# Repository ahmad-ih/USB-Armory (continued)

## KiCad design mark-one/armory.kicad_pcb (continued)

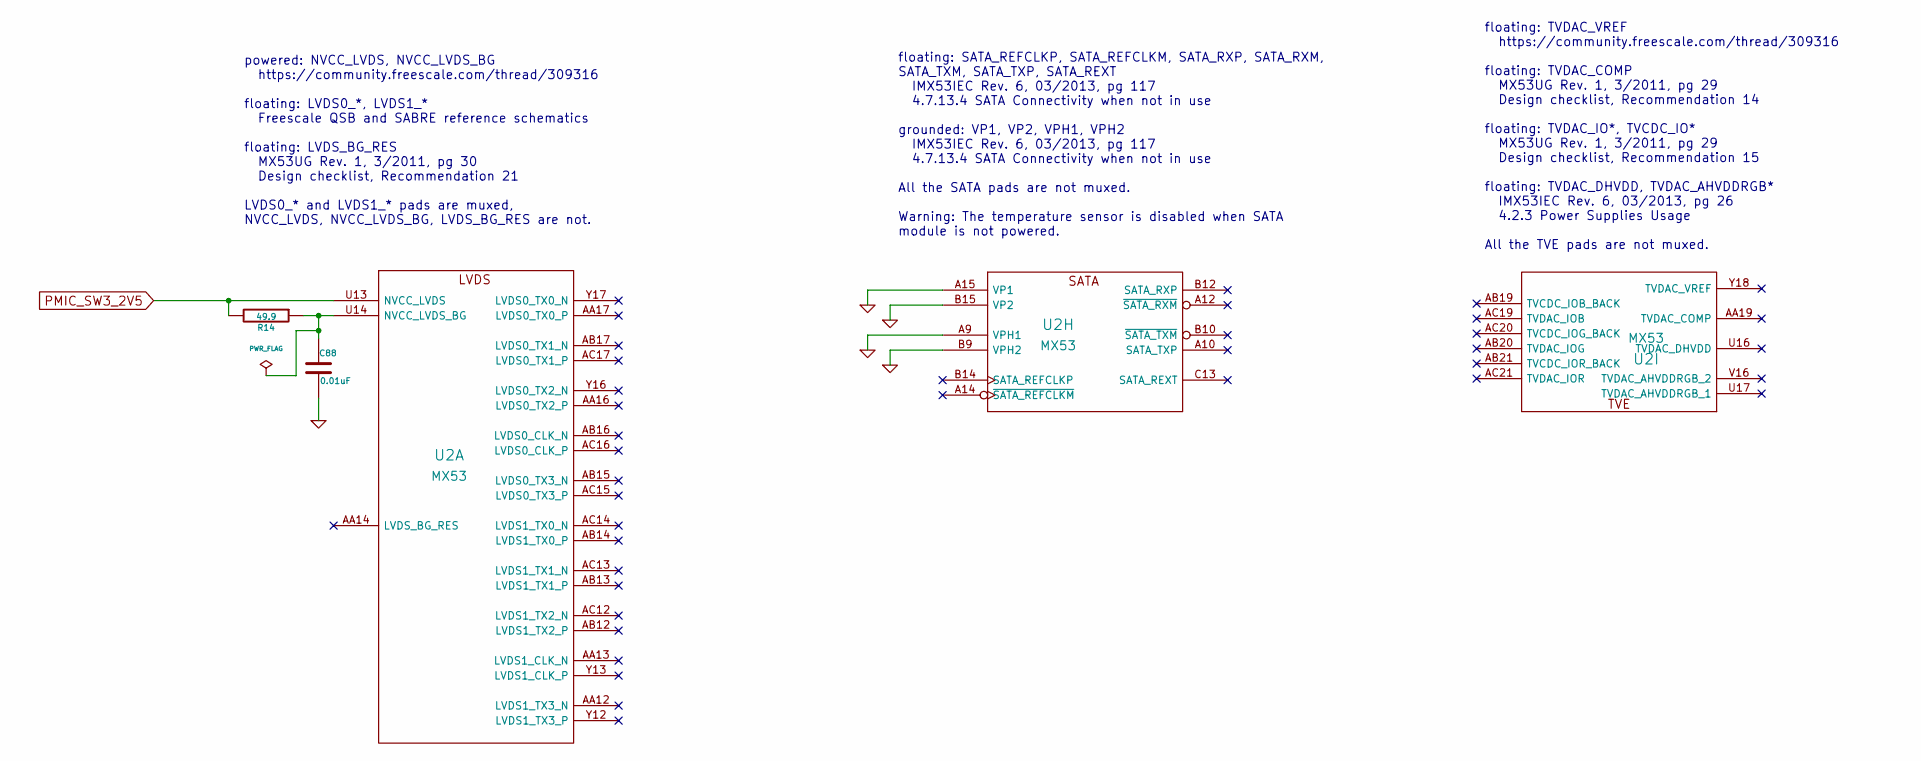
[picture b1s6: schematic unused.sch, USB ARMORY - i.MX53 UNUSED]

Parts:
C88: 0.01uF; SM0201; Mfg PN C0603X7R1A103K030BA
R14: 49.9; SM0201; Mfg PN CRCW020149R9FNED
U2: MX53

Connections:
GND: C88.2, U2.A9 (VPH1), U2.A15 (VP1), U2.B9 (VPH2), U2.B15 (VP2); also elsewhere on the board
unnamed: C88.1, R14.1, U2.U14 (NVCC_LVDS_BG)
PMIC_SW3_2V5: R14.2, U2.U13 (NVCC_LVDS); also elsewhere on the board

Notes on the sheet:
floating: TVDAC_VREF https://community.freescale.com/thread/309316 floating: TVDAC_COMP MX53UG Rev. 1, 3/2011, pg 29 Design checklist, Recommendation 14 floating: TVDAC_IO*, TVCDC_IO* MX53UG Rev. 1, 3/2011, pg 29 Design checklist, Recommendation 15 floating: TVDAC_DHVDD, TVDAC_AHVDDRGB* IMX53IEC Re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
powered: NVCC_LVDS, NVCC_LVDS_BG https://community.freescale.com/thread/309316 floating: LVDS0_*, LVDS1_* Freescale QSB and SABRE reference schematics floating: LVDS_BG_RES MX53UG Rev. 1, 3/2011, pg 30 Design checklist, Recommendation 21 LVDS0_* and LVDS1_* pads are muxed, NVCC_LVDS, NVCC_LVDS_BG, 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
floating: SATA_REFCLKP, SATA_REFCLKM, SATA_RXP, SATA_RXM, SATA_TXM, SATA_TXP, SATA_REXT IMX53IEC Rev. 6, 03/2013, pg 117 4.7.13.4 SATA Connectivity when not in use grounded: VP1, VP2, VPH1, VPH2 IMX53IEC Rev. 6, 03/2013, pg 117 4.7.13.4 SATA Connectivity when not in use All the SATA pads are not mu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

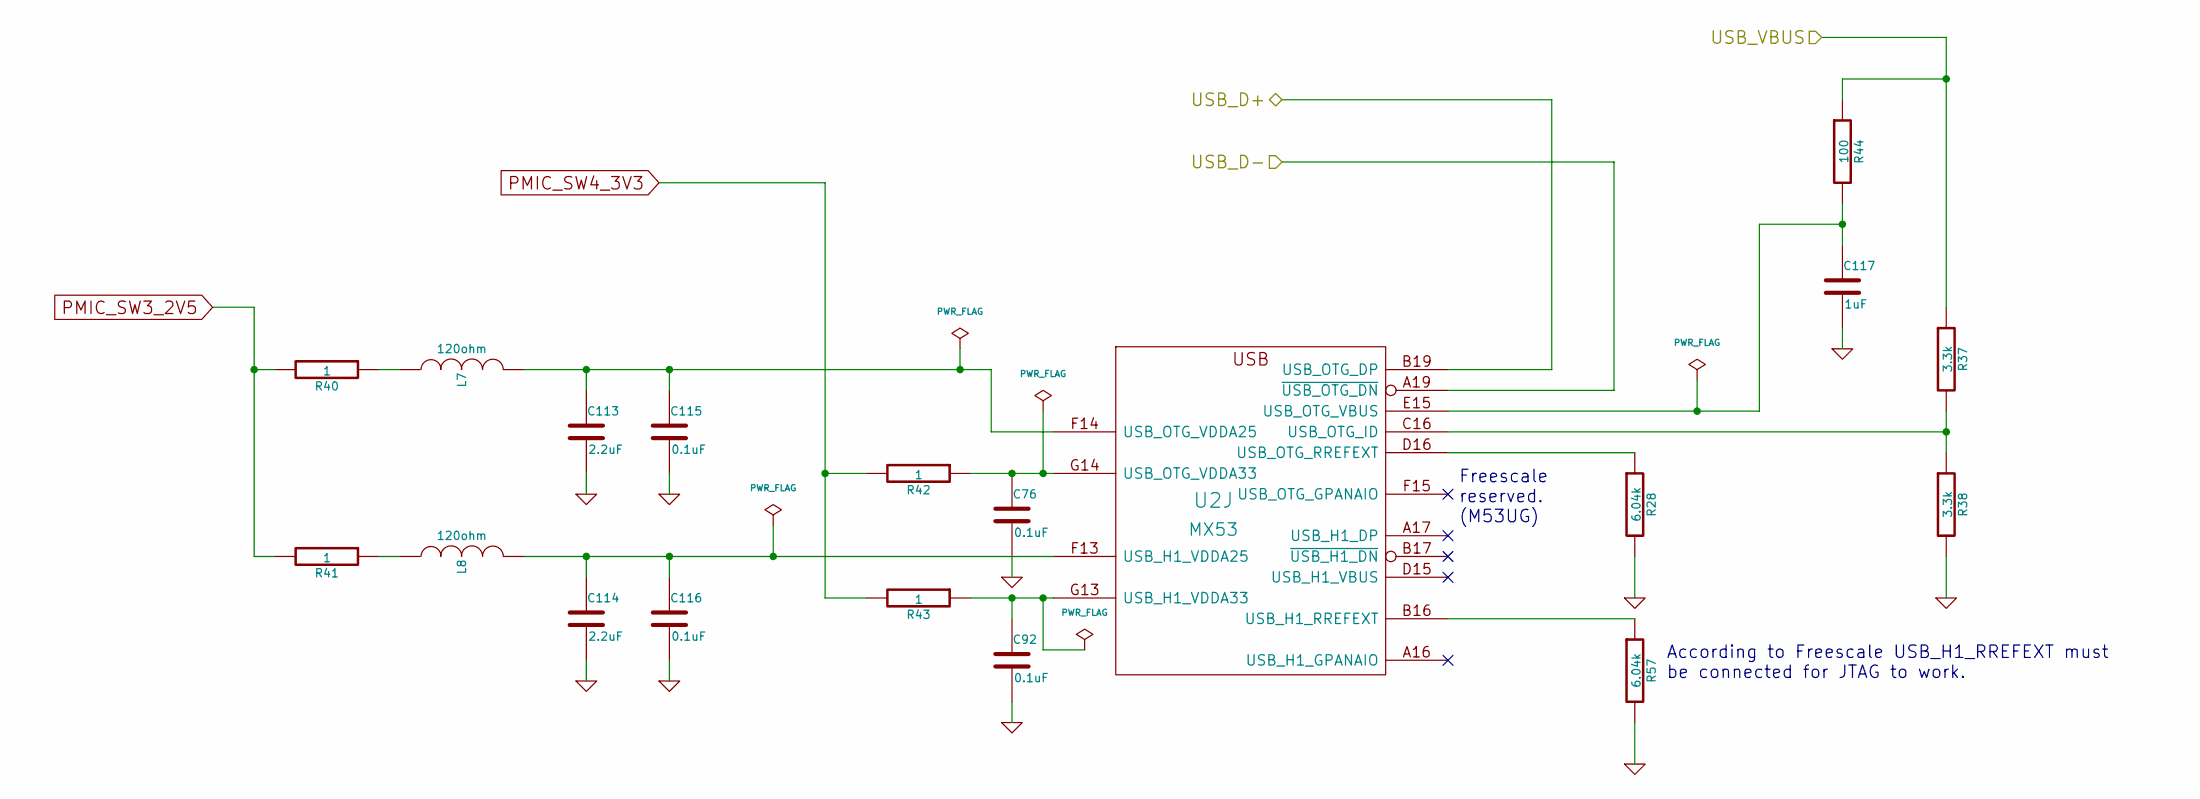
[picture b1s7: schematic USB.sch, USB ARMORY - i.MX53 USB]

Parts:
C76, C92, C115, C116: 0.1uF; SM0201; Mfg PN C0603X5R0J104K030BC
C113, C114: 2.2uF; SM0402; Mfg PN C1005X5R0J225K050BC
C117: 1uF; SM0201; Mfg PN C0603X5R0J105M030BC
L7, L8: 120ohm; SM0201; Mfg PN 742692003
R28, R57: 6.04k; SM0201; Mfg PN CRCW02016K04FNED
R37, R38: 3.3k; SM0201; Mfg PN CRCW02013K30FNED
R40, R41, R42, R43: 1; SM0201; Mfg PN MCRE000220
R44: 100; SM0201; Mfg PN CRCW0201100RFNED
U2: MX53

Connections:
/Interfaces/USB_VBUS: R37.1, R44.1; also elsewhere on the board
/USB/USB_D+: U2.B19 (USB_OTG_DP); also elsewhere on the board
/USB/USB_D-: U2.A19 (~USB_OTG_DN); also elsewhere on the board
GND: C76.2, C92.2, C113.2, C114.2, C115.2, C116.2, C117.2, R28.2, R38.2, R57.2; also elsewhere on the board
unnamed: C76.1, R42.1, U2.G14 (USB_OTG_VDDA33)
unnamed: C92.1, R43.1, U2.G13 (USB_H1_VDDA33)
unnamed: C113.1, C115.1, L7.2, U2.F14 (USB_OTG_VDDA25)
unnamed: C114.1, C116.1, L8.2, U2.F13 (USB_H1_VDDA25)
unnamed: C117.1, R44.2, U2.E15 (USB_OTG_VBUS)
unnamed: L7.1, R40.1
unnamed: L8.1, R41.1
unnamed: R28.1, U2.D16 (USB_OTG_RREFEXT)
unnamed: R37.2, R38.1, U2.C16 (USB_OTG_ID)
unnamed: R57.1, U2.B16 (USB_H1_RREFEXT)
PMIC_SW3_2V5: R40.2, R41.2; also elsewhere on the board
PMIC_SW4_3V3: R42.2, R43.2; also elsewhere on the board

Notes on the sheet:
Freescale reserved. (M53UG)
According to Freescale USB_H1_RREFEXT must be connected for JTAG to work.

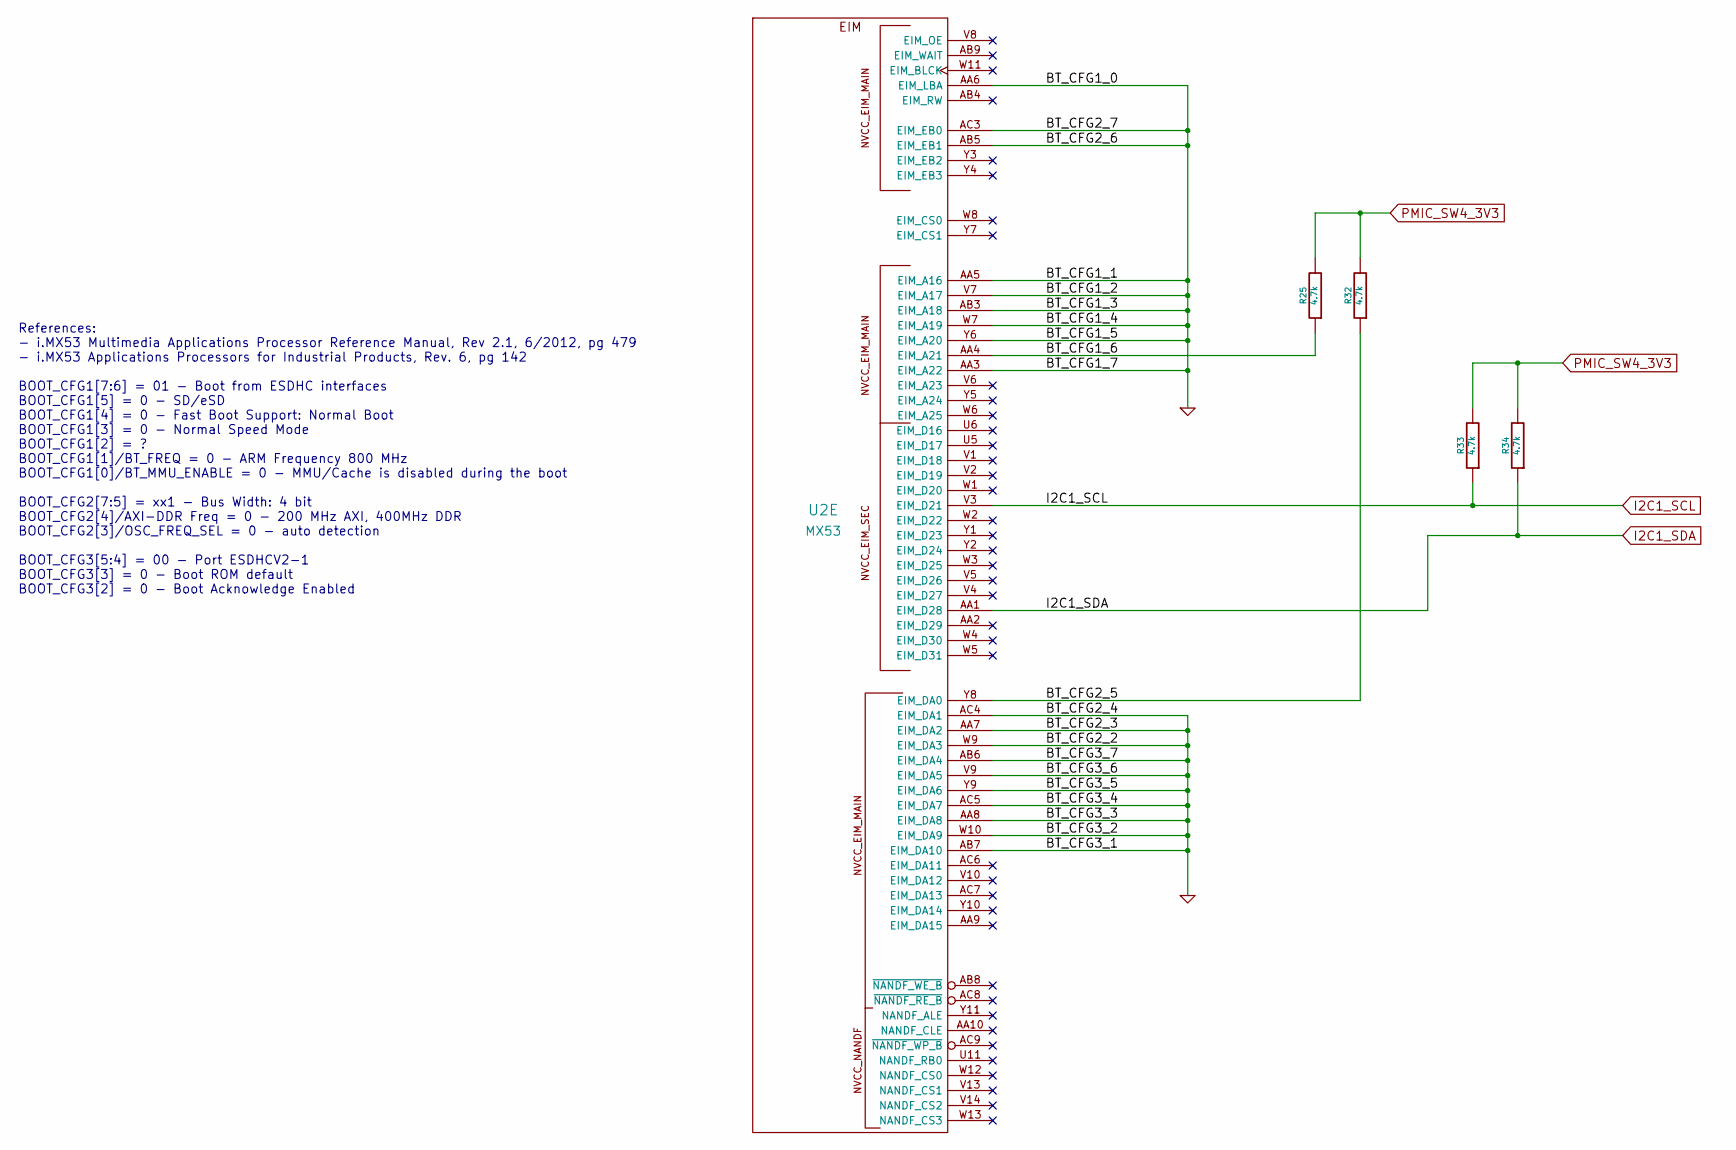
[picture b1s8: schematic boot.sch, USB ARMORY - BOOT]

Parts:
R25, R32, R33, R34: 4.7k; SM0201; Mfg PN CRCW02014K70FNED
U2: MX53

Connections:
/Boot/BT_CFG1_6: R25.1, U2.AA4 (EIM_A21)
/Boot/BT_CFG2_5: R32.1, U2.Y8 (EIM_DA0)
GND: U2.AA3 (EIM_A22), U2.AA5 (EIM_A16), U2.AA6 (EIM_LBA), U2.AA7 (EIM_DA2), U2.AA8 (EIM_DA8), U2.AB3 (EIM_A18), U2.AB5 (EIM_EB1), U2.AB6 (EIM_DA4), U2.AB7 (EIM_DA10), U2.AC3 (EIM_EB0), U2.AC4 (EIM_DA1), U2.AC5 (EIM_DA7), U2.V7 (EIM_A17), U2.V9 (EIM_DA5), U2.W7 (EIM_A19), U2.W9 (EIM_DA3), U2.W10 (EIM_DA9), U2.Y6 (EIM_A20), U2.Y9 (EIM_DA6); also elsewhere on the board
I2C1_SCL: R33.1, U2.V3 (EIM_D21)
I2C1_SDA: R34.1, U2.AA1 (EIM_D28)
PMIC_SW4_3V3: R25.2, R32.2, R33.2, R34.2; also elsewhere on the board

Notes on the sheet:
References: - i.MX53 Multimedia Applications Processor Reference Manual, Rev 2.1, 6/2012, pg 479 - i.MX53 Applications Processors for Industrial Products, Rev. 6, pg 142 BOOT_CFG1[7:6] = 01 - Boot from ESDHC interfaces BOOT_CFG1[5] = 0 - SD/eSD BOOT_CFG1[4] = 0 - Fast Boot Support: Normal Boot BOOT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

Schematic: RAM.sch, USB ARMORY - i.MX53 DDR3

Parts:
C89, C90, C91, C93, C94, C96, C97, C98, C100, C101, C102, C104: 0.1uF; SM0201; Mfg PN C0603X5R0J104K030BC
C95, C99, C103: 0.01uF; SM0201; Mfg PN C0603X7R1A103K030BA
C105, C106: 10uF; SM0603; Mfg PN C1608X5R1A106K080AC
P3: TST; TP
R15, R24: 470; SM0201; Mfg PN CRCW0201470RFNED
R27, R29: 240; SM0201; Mfg PN CRCW0201240RFNED
R30: 100; SM0603; Mfg PN CRCW0603100RFKEA
U2: MX53
U4: MT41K256M16HA; micron-96-fbga-ha; Mfg PN MT41K256M16HA-107

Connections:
/RAM/DDR_VREF: C89.1, C90.2, C91.1, C93.1, P3.1, R15.1, R24.2, U2.L17 (DDR_VREF), U4.H1 (VREFDQ), U4.M8 (VREFCA)
/RAM/DDR_ZQ: R29.2, U4.L8 (ZQ)
/RAM/DRAM_A0: U2.M19 (DRAM_A0), U4.N3 (A0)
/RAM/DRAM_A1: U2.L21 (DRAM_A1), U4.P7 (A1)
/RAM/DRAM_A2: U2.M20 (DRAM_A2), U4.P3 (A2)
/RAM/DRAM_A3: U2.N20 (DRAM_A3), U4.N2 (A3)
/RAM/DRAM_A4: U2.K20 (DRAM_A4), U4.P8 (A4)
/RAM/DRAM_A5: U2.N21 (DRAM_A5), U4.P2 (A5)
/RAM/DRAM_A6: U2.M22 (DRAM_A6), U4.R8 (A6)
/RAM/DRAM_A7: U2.N22 (DRAM_A7), U4.R2 (A7)
/RAM/DRAM_A8: U2.N23 (DRAM_A8), U4.T8 (A8)
/RAM/DRAM_A9: U2.M21 (DRAM_A9), U4.R3 (A9)
/RAM/DRAM_A10: U2.K19 (DRAM_A10), U4.L7 (A10/AP)
/RAM/DRAM_A11: U2.L22 (DRAM_A11), U4.R7 (A11)
/RAM/DRAM_A12: U2.L20 (DRAM_A12), U4.N7 (A12/~BC)
/RAM/DRAM_A13: U2.L23 (DRAM_A13), U4.T3 (A13)
/RAM/DRAM_A14: U2.N18 (DRAM_A14), U4.T7 (A14)
/RAM/DRAM_CALIBRATION: R27.2, U2.M23 (DRAM_CALIBRATION)
/RAM/DRAM_CAS: U2.L18 (DRAM_CAS), U4.K3 (~CAS)
/RAM/DRAM_CS0: U2.K18 (DRAM_CS0), U4.L2 (~CS)
/RAM/DRAM_D0: U2.H20 (DRAM_D0), U4.E3 (DQ0)
/RAM/DRAM_D1: U2.G21 (DRAM_D1), U4.F7 (DQ1)
/RAM/DRAM_D2: U2.J21 (DRAM_D2), U4.F2 (DQ2)
/RAM/DRAM_D3: U2.G20 (DRAM_D3), U4.F8 (DQ3)
/RAM/DRAM_D4: U2.J23 (DRAM_D4), U4.H3 (DQ4)
/RAM/DRAM_D5: U2.G23 (DRAM_D5), U4.H8 (DQ5)
/RAM/DRAM_D6: U2.J22 (DRAM_D6), U4.G2 (DQ6)
/RAM/DRAM_D7: U2.G22 (DRAM_D7), U4.H7 (DQ7)
/RAM/DRAM_D8: U2.E21 (DRAM_D8), U4.D7 (DQ8)
/RAM/DRAM_D9: U2.D21 (DRAM_D9), U4.C3 (DQ9)
/RAM/DRAM_D10: U2.E22 (DRAM_D10), U4.C8 (DQ10)
/RAM/DRAM_D11: U2.D20 (DRAM_D11), U4.C2 (DQ11)
/RAM/DRAM_D12: U2.E23 (DRAM_D12), U4.A7 (DQ12)
/RAM/DRAM_D13: U2.C23 (DRAM_D13), U4.A2 (DQ13)
/RAM/DRAM_D14: U2.F23 (DRAM_D14), U4.B8 (DQ14)
/RAM/DRAM_D15: U2.C22 (DRAM_D15), U4.A3 (DQ15)
/RAM/DRAM_DQM0: U2.H21 (DRAM_DQM0), U4.E7 (LDM)
/RAM/DRAM_DQM1: U2.E20 (DRAM_DQM1), U4.D3 (UDM)
/RAM/DRAM_RAS: U2.J19 (DRAM_RAS), U4.J3 (~RAS)
/RAM/DRAM_RESET: U2.P18 (DRAM_RESET), U4.T2 (~RESET)
/RAM/DRAM_SDBA0: U2.R19 (DRAM_SDBA0), U4.M2 (BA0)
/RAM/DRAM_SDBA1: U2.P20 (DRAM_SDBA1), U4.N8 (BA1)
/RAM/DRAM_SDBA2: U2.N19 (DRAM_SDBA2), U4.M3 (BA2)
/RAM/DRAM_SDCKE0: U2.H19 (DRAM_SDCKE0), U4.K9 (CKE)
/RAM/DRAM_SDCLK_0: R30.1, U2.K23 (DRAM_SDCLK_0), U4.J7 (CK)
/RAM/DRAM_SDCLK_0_B: R30.2, U2.K22 (~DRAM_SDCLK_0_B), U4.K7 (~CK)
/RAM/DRAM_SDODT0: U2.J18 (DRAM_SDODT0), U4.K1 (ODT)
/RAM/DRAM_SDQS0: U2.H23 (DRAM_SDQS0), U4.F3 (LDQS)
/RAM/DRAM_SDQS0_B: U2.H22 (~DRAM_SDQS0_B), U4.G3 (~LDQS)
/RAM/DRAM_SDQS1: U2.D23 (DRAM_SDQS1), U4.C7 (UDQS)
/RAM/DRAM_SDQS1_B: U2.D22 (~DRAM_SDQS1_B), U4.B7 (~UDQS)
/RAM/DRAM_WE: U2.L19 (DRAM_SDWE), U4.L3 (~WE)
GND: C89.2, C91.2, C93.2, C94.2, C95.2, C96.2, C97.2, C98.2, C99.2, C100.2, C101.2, C102.2, C103.2, C104.2, C105.2, C106.2, R24.1, R27.1, R29.1, U4.A9 (VSS1), U4.B1 (VSSQ1), U4.B3 (VSS2), U4.B9 (VSSQ2), U4.D1 (VSSQ3), U4.D8 (VSSQ4), U4.E1 (VSS3), U4.E2 (VSSQ5), U4.E8 (VSSQ6), U4.F9 (VSSQ7), U4.G1 (VSSQ8), U4.G8 (VSS4), U4.G9 (VSSQ9), U4.J2 (VSS5), U4.J8 (VSS6), U4.M9 (VSS8), U4.P1 (VSS9), U4.P9 (VSS10), U4.T1 (VSS11), U4.T9 (VSS12); also elsewhere on the board
PMIC_DDR_1V5: C90.1, C94.1, C95.1, C96.1, C97.1, C98.1, C99.1, C100.1, C101.1, C102.1, C103.1, C104.1, C105.1, C106.1, R15.2, U4.A1 (VDDQ1), U4.A8 (VDDQ2), U4.B2 (VDD1), U4.C1 (VDDQ3), U4.C9 (VDDQ4), U4.D2 (VDDQ5), U4.D9 (VDD2), U4.E9 (VDDQ6), U4.F1 (VDDQ7), U4.G7 (VDD3), U4.H2 (VDDQ8), U4.H9 (VDDQ9), U4.K2 (VDD4), U4.K8 (VDD5), U4.N1 (VDD6), U4.N9 (VDD7), U4.R1 (VDD8), U4.R9 (VDD9); also elsewhere on the board

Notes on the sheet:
Place near the VDD balls.
Place near the VDDQ balls.

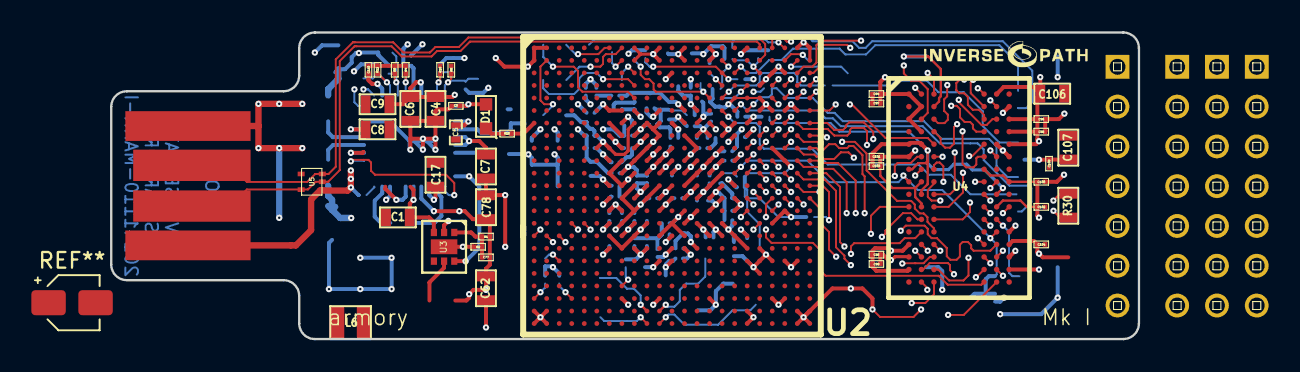
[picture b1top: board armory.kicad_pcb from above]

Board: 8 copper layers, 65.6 x 19.6 mm, 183 parts (0 on the bottom side), 119 nets.

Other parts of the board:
P4#2, P4#3, P4#4: CONN_01X07; pinhead-1X7
Ref**: Val**; LOGO_SMALL

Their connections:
/Interfaces/GPIO5_26: P4#4.3; also elsewhere on the board
/Interfaces/GPIO5_27: P4#4.4; also elsewhere on the board
/Interfaces/GPIO5_30: P4#4.7; also elsewhere on the board
/Interfaces/UART1_RX: P4#4.6; also elsewhere on the board
/Interfaces/UART1_TX: P4#4.5; also elsewhere on the board
/Interfaces/USB_VBUS: P4#4.2; also elsewhere on the board
GND: P4#4.1; also elsewhere on the board

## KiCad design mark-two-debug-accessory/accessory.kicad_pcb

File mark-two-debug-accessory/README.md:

USB armory Mk II debug accessory
================================

USB armory | https://github.com/inversepath/usbarmory  
Copyright (c) F-Secure Corporation

The USB armory from [F-Secure Foundry](https://foundry.f-secure.com) is an open
source hardware design, implementing a flash drive sized computer.

The USB armory Mk II exposes a USB Type-C receptacle, which allows through the
so called USB-C 'debug accessory mode' to route analog/debug signals over its
connector, the USB armory Mk II design leverages on this to break out UART,
SPI, I²C, CAN (pre-transceiver), GPIOs connections to/from its application
processor.

The debug accessory board allows to access UART and GPIO signals through USB,
without requiring probes, through an FTDI FT4232H. This allows, for example,
access to the USB armory Mk II serial console without wires or probes, natively
using only USB cables. All other interfaces can be accessed through dedicated
breakout through holes.

This repository is aimed towards developers, if you wish to purchase a USB
armory board please see the [USB armory project page](https://www.f-secure.com/en/consulting/foundry/usb-armory).

PCB Information
===============

2 layers, 0.80mm thickness, top only components  
Outer layers 0.5 oz base copper foil  
Inner layers   1 oz base copper foil  
width (X) 45.65 mm, height (Y) 25.90 mm  
Red soldermask, white component legend

[Bill of materials](https://inversepath.github.io/BOM/usbarmory-mark-two-debug-accessory.html)

DRC information
---------------

Minimum track width:            0.127 mm  
Minimum via diameter:           0.450 mm  
Outer layer track width:        0.127 mm  
Outer layer isolation distance: 0.127 mm  
Outer layer annular ring:       0.100 mm  
Smallest final hole (plated):   0.150 mm

USB armory Mk II debug I/Os
===========================

*NOTE*: the connection between the debug accessory and the target is supported
only with the same orientation for both top layers (side with components for
the accessory, side with LEDs for the USB armory).

The following table summarizes the available configurations on the USB armory
Mk II through debug accessory mode, which are exposed on its Type-C receptacle
port.

|  USB-C pin   | MUX mode ALT0 | MUX mode ALT8 | MUX mode ALT2 | MUX mode ALT5 |
|:-------------|---------------|---------------|---------------|---------------|
| SSTXp1 (A2)  | UART2_TX      | ECSPI3_SSO    | I2C4_SCL¹     | GPIO1_IO20   |
| SSTXn1 (A3)  | UART2_RX      | ECSPI3_SCLK   | I2C4_SDA¹     | GPIO1_IO21    |
| SSRXp1 (B11) | UART2_RTS_B   | ECSPI3_MISO   | FLEXCAN2_RX¹  | GPIO1_IO23    |
| SSRXn1 (B10) | UART2_CTS_B   | ECSPI3_MOSI   | FLEXCAN2_TX¹  | GPIO1_IO22    |
| SSRXp2 (A11) | UART4_TX      | ECSPI2_SCLK   | I2C1_SCL      | GPIO1_IO28    |
| SSTXn2 (B3)  | UART4_RX      | ECSPI2_SSO    | I2C1_SDA      | GPIO1_IO29    |
| SSRXn2 (A10) | UART5_TX~     | ECSPI2_MOSI   | I2C2_SCL      | GPIO1_IO30    |
| SSTXp2 (B2)  | UART5_RX~     | ECSPI2_MISO   | I2C2_SDA      | GPIO1_IO31    |

¹ Only on USB armory Mk II boards mounting i.MX6UL SoC, not available on
  versions mounting the i.MX6ULZ.

Debug accessory jumper settings
===============================

Power source
------------

The debug accessory always acts as a power source and is meant to be connected
exclusively to the USB armory Mk II Type-C receptacle port. The USB armory Mk
II Type-C can be safely plugged on a different receptacle as the board can
handle two power sources simultaneously.

It is not recommended to connect the debug accessory to anything other than the
USB armory Mk II, however in case this happens compliant Type-C receptacles
should handle the situation gracefully¹ without concerns.

¹ USB Type-C Cable and Connector Specification (1.3, 2017-07-14):
  "Legacy hosts/chargers that by default source VBUS when connected using any
  legacy USB connector (Standard-A, Micro-B, etc.) to USB Type-C cable or adapter
  are exempted from these two requirements."

I/O mode
--------

The GPIO and UART functions can be used directly using the FTDI FT4232H USB
interface accessible on the Micro USB Type-B connector, all other modes can be
accessed using the exposed breakout through holes.

The following table illustrates the required jumper positions and interfaces
for each available I/O mode.

| Mode  | GPIO¹ | Interface
|:------|-------|-----------------------------------|
| GPIO  |  GPIO | FTDI MPSSE mode on [A,B]DBUS[4-7] |
| UART2 | !GPIO | FTDI RS232 mode on CDBUS[0-3]     |
| UART4 | !GPIO | FTDI RS232 mode on BDBUS[0-1]     |
| UART5 | !GPIO | FTDI RS232 mode on ADBUS[0-1]     |
| SPI2  |  N/A² | through holes: A11, B3, A10, B2   |
| SPI3  |  N/A² | through holes: A2,  A3, B11, B10  |
| I2C1  |  N/A² | through holes: A11, B3            |
| I2C2  |  N/A² | through holes: A10, B2            |
| I2C4  |  N/A² | through holes: A2,  A3            |
| CAN2  |  N/A² | through holes: B11, B10           |

¹ The GPIO header position refers to termination either of the two pins facing
  the "GPIO" label (GPIO position, pins towards positions 3 and 2) or the
  opposite position (!GPIO position, pins towards positions 2 and 1).

² Any position can be used as the FTDI is not used in such mode.

Pin assignment: GPIO
====================

|  USB-C pin   | i.MX6UL pin | FTDI pin | FTDI MPSSE |
|:-------------|-------------|----------|------------|
| SSTXp1 (A2)  | GPIO1_IO20  | BDBUS6   | #B GPIOL2  |
| SSTXn1 (A3)  | GPIO1_IO21  | BDBUS7   | #B GPIOL3  |
| SSRXp1 (B11) | GPIO1_IO23  | BDBUS5   | #B GPIOL1  |
| SSRXn1 (B10) | GPIO1_IO22  | BDBUS4   | #B GPIOL0  |
| SSRXp2 (A11) | GPIO1_IO28  | ADBUS4   | #A GPIOL0  |
| SSTXn2 (B3)  | GPIO1_IO29  | ADBUS7   | #A GPIOL3  |
| SSRXn2 (A10) | GPIO1_IO30  | ADBUS5   | #A GPIOL1  |
| SSTXp2 (B2)  | GPIO1_IO31  | ADBUS6   | #A GPIOL2  |

Pin assignment: UART2
=====================

|  USB-C pin   | i.MX6UL pin | FTDI pin | FTDI MPSSE |
|:-------------|-------------|----------|------------|
| SSTXp1 (A2)  | UART2_TX    | CDBUS1   | #C RXD     |
| SSTXn1 (A3)  | UART2_RX    | CDBUS0   | #C TXD     |
| SSRXp1 (B11) | UART2_RTS_B | CDBUS3   | #C CTS     |
| SSRXn1 (B10) | UART2_CTS_B | CDBUS2   | #C RTS     |

Pin assignment: UART4
=====================

|  USB-C pin   | i.MX6UL pin | FTDI pin | FTDI MPSSE |
|:-------------|-------------|----------|------------|
| SSRXp2 (A11) | UART4_TX    | BDBUS1   | #B RXD     |
| SSTXn2 (B3)  | UART4_RX    | BDBUS0   | #B TXD     |

Pin assignment: UART5
=====================

|  USB-C pin   | i.MX6UL pin | FTDI pin | FTDI MPSSE |
|:-------------|-------------|----------|------------|
| SSRXn2 (A10) | UART5_TX    | ADBUS1   | #A RXD     |
| SSTXp2 (B2)  | UART5_RX    | ADBUS0   | #A TXD     |

License
=======

USB armory | https://github.com/inversepath/usbarmory  
Copyright (c) F-Secure Corporation

This is an open hardware design licensed under the terms of the CERN Open
Hardware Licence (OHL) v1.2.

You may redistribute and modify this documentation under the terms of the CERN
OHL v.1.2 (http://ohwr.org/cernohl). This documentation is distributed WITHOUT
ANY EXPRESS OR IMPLIED WARRANTY, INCLUDING OF MERCHANTABILITY, SATISFACTORY
QUALITY AND FITNESS FOR A PARTICULAR PURPOSE. Please see the CERN OHL v.1.2 for
applicable conditions.

The following exceptions apply:

- `../lib.snapeda`: all files in this directory are imported or modified
  from SnapEDA symbols and footprints, therefore the license at
  https://www.snapeda.com/about/FAQ/#license applies.

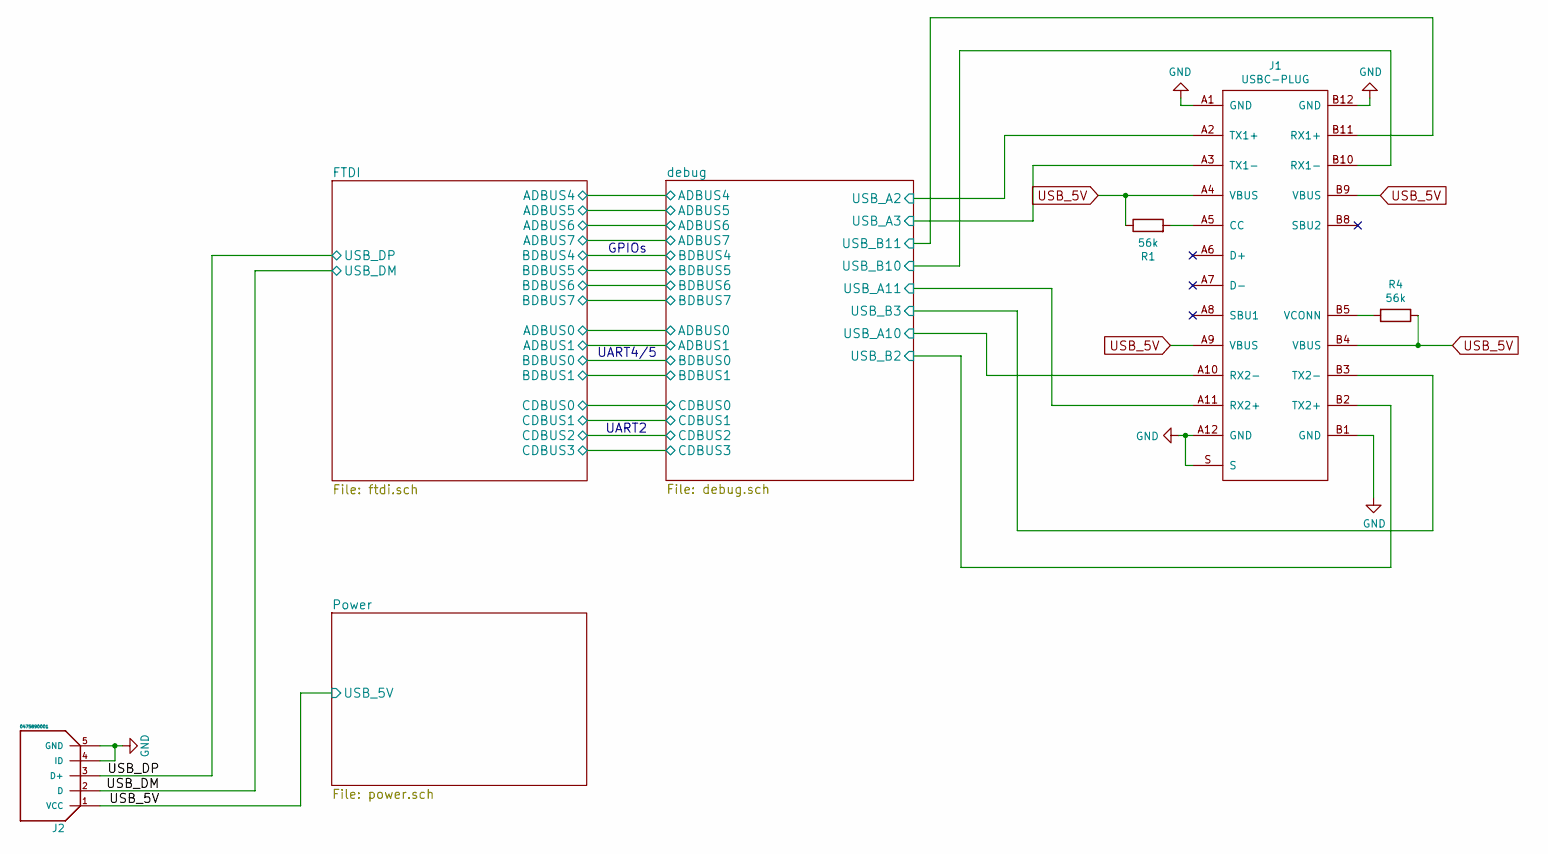
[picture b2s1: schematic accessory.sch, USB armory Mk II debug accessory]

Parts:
J1: USBC-PLUG; WURTH_632712000011; Mfg PN 632712000011
J2: 0475890001; MOLEX_0475890001; Mfg PN 0475890001
R1, R4: 56k; SM0603; Mfg PN MCT06030C5602FP500

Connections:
/USB_DM: J2.2 (D); also elsewhere on the board
/USB_DP: J2.3 (D+); also elsewhere on the board
/debug/USB_A2: J1.A2 (TX1+); also elsewhere on the board
/debug/USB_A3: J1.A3 (TX1-); also elsewhere on the board
/debug/USB_A10: J1.A10 (RX2-); also elsewhere on the board
/debug/USB_A11: J1.A11 (RX2+); also elsewhere on the board
/debug/USB_B2: J1.B2 (TX2+); also elsewhere on the board
/debug/USB_B3: J1.B3 (TX2-); also elsewhere on the board
/debug/USB_B10: J1.B10 (RX1-); also elsewhere on the board
/debug/USB_B11: J1.B11 (RX1+); also elsewhere on the board
GND: J1.A1 (GND), J1.A12 (GND), J1.B1 (GND), J1.B12 (GND), J1.S, J2.4 (ID), J2.5 (GND); also elsewhere on the board
unnamed: J1.A5 (CC), R1.2
unnamed: J1.B5 (VCONN), R4.2
USB_5V: J1.A4 (VBUS), J1.A9 (VBUS), J1.B4 (VBUS), J1.B9 (VBUS), J2.1 (VCC), R1.1, R4.1; also elsewhere on the board

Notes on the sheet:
GPIOs
UART4/5
UART2

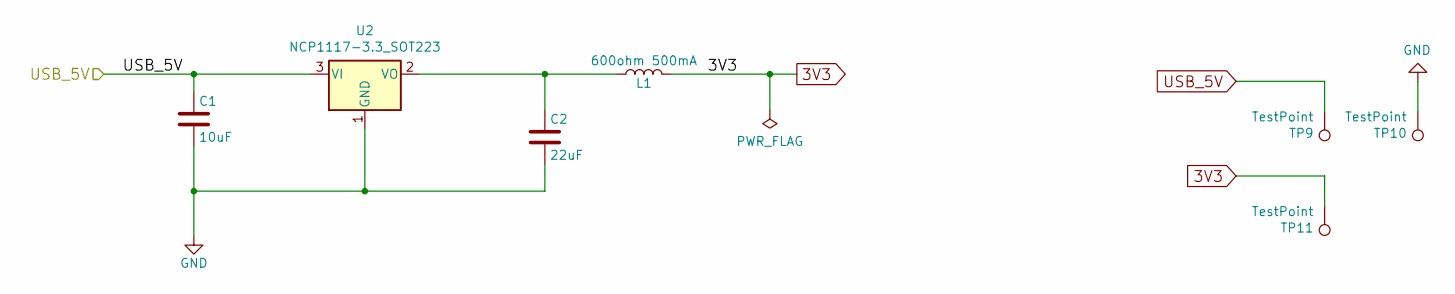
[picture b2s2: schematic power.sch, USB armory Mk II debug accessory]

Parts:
C1: 10uF; SM0603; Mfg PN C1608X5R1A106M080AC
C2: 22uF; SM0603; Mfg PN C1608X5R1A226M080AC
L1: 600ohm 500mA; SM0603; Mfg PN BLM18AG601SN1D
TP9, TP10, TP11: TestPoint; CONN_1
U2: NCP1117-3.3_SOT223; SOT-223; Mfg PN NCP1117ST33T3G

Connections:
3V3: L1.2, TP11.1; also elsewhere on the board
GND: C1.2, C2.2, TP10.1, U2.1 (GND); also elsewhere on the board
unnamed: C2.1, L1.1, U2.2 (VO)
USB_5V: C1.1, TP9.1, U2.3 (VI); also elsewhere on the board

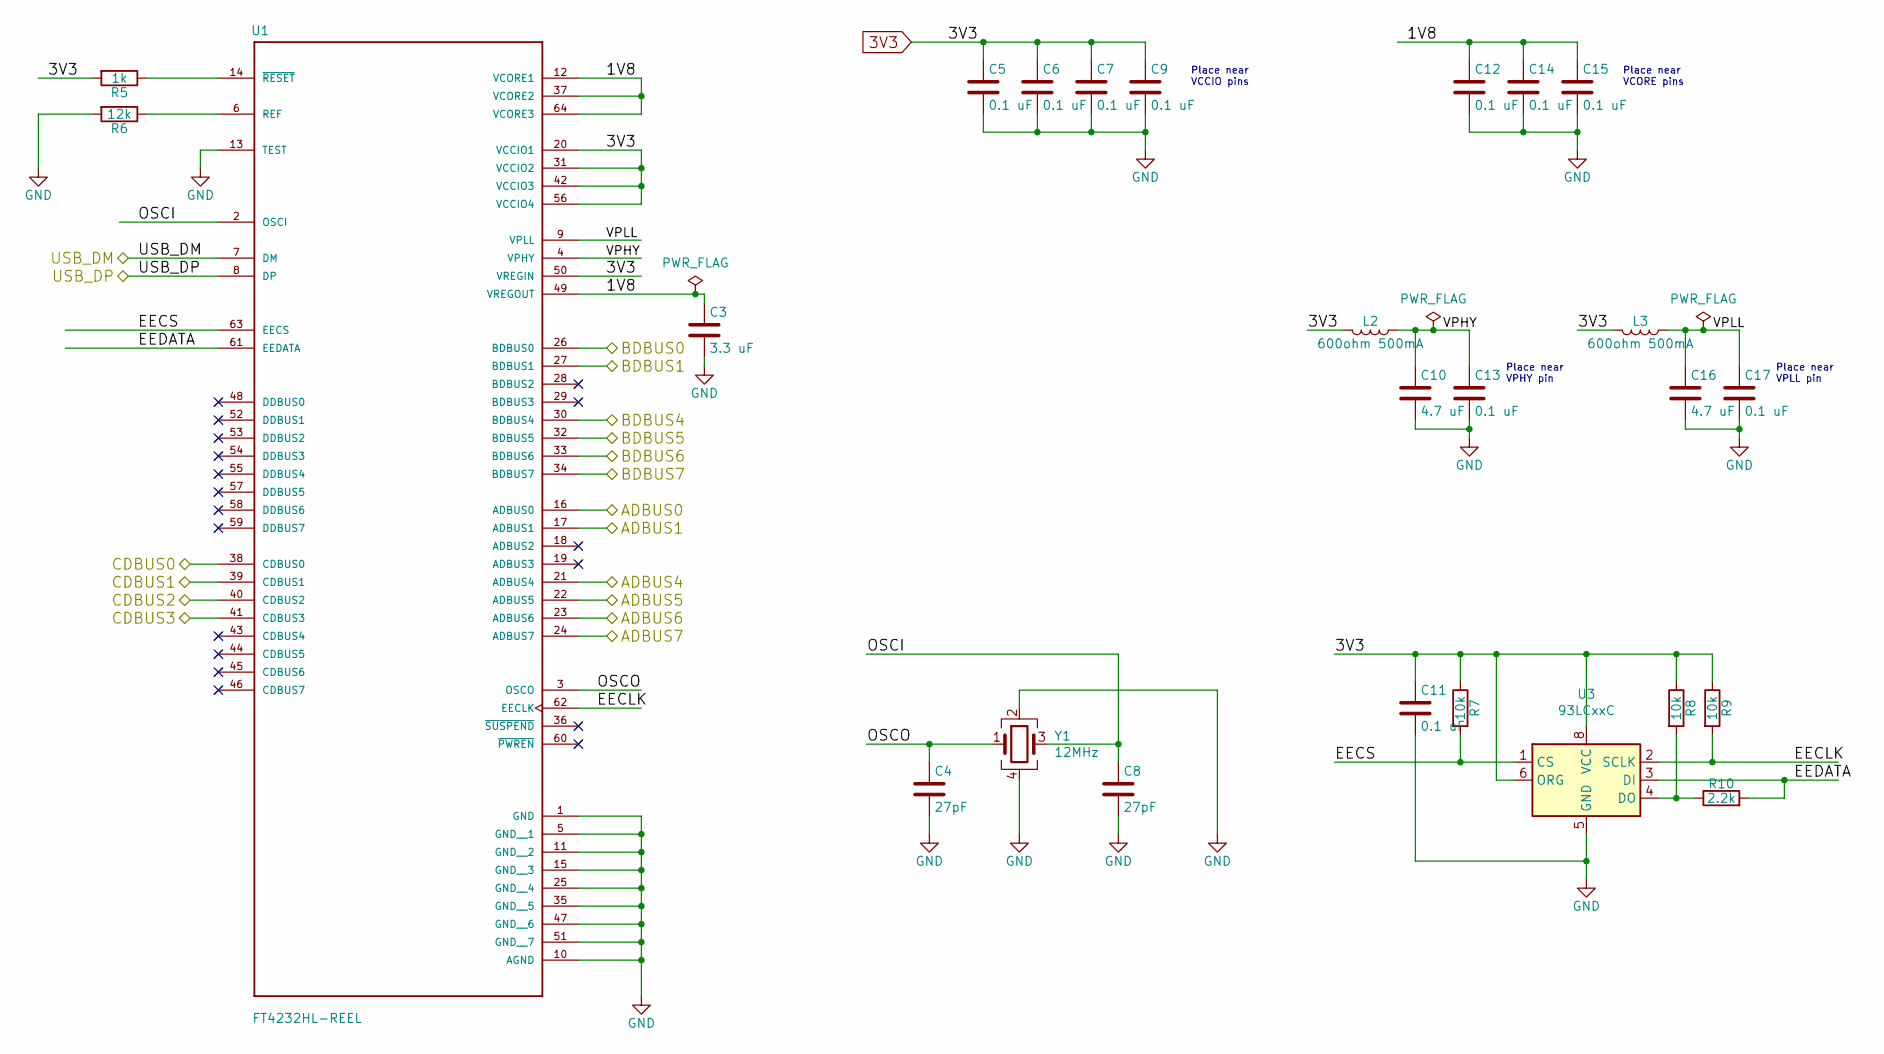
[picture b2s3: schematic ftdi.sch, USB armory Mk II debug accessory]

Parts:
C3: 3.3 uF; SM0603; Mfg PN C1608X5R1C335K080AC
C4, C8: 27pF; SM0603; Mfg PN GRM1885C1H270FA01D
C5, C6, C7, C9, C11, C12, C13, C14, C15, C17: 0.1 uF; SM0603; Mfg PN C1608X7R1E104K080AA
C10, C16: 4.7 uF; SM0603; Mfg PN CGB3B1X5R1A475M055AC
L2, L3: 600ohm 500mA; SM0603; Mfg PN BLM18AG601SN1D
R5: 1k; SM0603; Mfg PN RCA06031K00FKEAHP
R6: 12k; SM0603; Mfg PN CRCW060312K0FKEAC
R7, R8, R9: 10k; SM0603; Mfg PN CRCW060310K0FKEA
R10: 2.2k; SM0603; Mfg PN RCS06032K20JNEA
U1: FT4232HL-REEL; QFP50P1200X1200X160-64N; Mfg PN FT4232HL-REEL
U3: 93LCxxC; 8L_SOIC_Narrow_3_90_SN_C04-057C; Mfg PN 93LC56C-I/SN
Y1: 12MHz; TXC-3.2x2.5; Mfg PN 7M-12.000MAAJ-T

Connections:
3V3: C5.1, C6.1, C7.1, C9.1, C11.1, L2.1, L3.1, R5.2, R7.1, R8.1, R9.1, U1.20 (VCCIO1), U1.31 (VCCIO2), U1.42 (VCCIO3), U1.50 (VREGIN), U1.56 (VCCIO4), U3.6 (ORG), U3.8 (VCC); also elsewhere on the board
/FTDI/1V8: C3.1, C12.1, C14.1, C15.1, U1.12 (VCORE1), U1.37 (VCORE2), U1.49 (VREGOUT), U1.64 (VCORE3)
/FTDI/ADBUS0: U1.16 (ADBUS0); also elsewhere on the board
/FTDI/ADBUS1: U1.17 (ADBUS1); also elsewhere on the board
/FTDI/ADBUS4: U1.21 (ADBUS4); also elsewhere on the board
/FTDI/ADBUS5: U1.22 (ADBUS5); also elsewhere on the board
/FTDI/ADBUS6: U1.23 (ADBUS6); also elsewhere on the board
/FTDI/ADBUS7: U1.24 (ADBUS7); also elsewhere on the board
/FTDI/BDBUS0: U1.26 (BDBUS0); also elsewhere on the board
/FTDI/BDBUS1: U1.27 (BDBUS1); also elsewhere on the board
/FTDI/BDBUS4: U1.30 (BDBUS4); also elsewhere on the board
/FTDI/BDBUS5: U1.32 (BDBUS5); also elsewhere on the board
/FTDI/BDBUS6: U1.33 (BDBUS6); also elsewhere on the board
/FTDI/BDBUS7: U1.34 (BDBUS7); also elsewhere on the board
/FTDI/CDBUS0: U1.38 (CDBUS0); also elsewhere on the board
/FTDI/CDBUS1: U1.39 (CDBUS1); also elsewhere on the board
/FTDI/CDBUS2: U1.40 (CDBUS2); also elsewhere on the board
/FTDI/CDBUS3: U1.41 (CDBUS3); also elsewhere on the board
/FTDI/EECLK: R9.2, U1.62 (EECLK), U3.2 (SCLK)
/FTDI/EECS: R7.2, U1.63 (EECS), U3.1 (CS)
/FTDI/EEDATA: R10.2, U1.61 (EEDATA), U3.3 (DI)
/FTDI/OSCI: C8.1, U1.2 (OSCI), Y1.3
/FTDI/OSCO: C4.1, U1.3 (OSCO), Y1.1
/FTDI/VPHY: C10.1, C13.1, L2.2, U1.4 (VPHY)
/FTDI/VPLL: C16.1, C17.1, L3.2, U1.9 (VPLL)
/USB_DM: U1.7 (DM); also elsewhere on the board
/USB_DP: U1.8 (DP); also elsewhere on the board
GND: C3.2, C4.2, C5.2, C6.2, C7.2, C8.2, C9.2, C10.2, C11.2, C12.2, C13.2, C14.2, C15.2, C16.2, C17.2, R6.2, U1.1 (GND), U1.5 (GND__1), U1.10 (AGND), U1.11 (GND__2), U1.13 (TEST), U1.15 (GND__3), U1.25 (GND__4), U1.35 (GND__5), U1.47 (GND__6), U1.51 (GND__7), U3.5 (GND), Y1.2, Y1.4; also elsewhere on the board
unnamed: R5.1, U1.14 (~RESET~)
unnamed: R6.1, U1.6 (REF)
unnamed: R8.2, R10.1, U3.4 (DO)

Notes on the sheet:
Place near VCORE pins
Place near VCCIO pins
Place near VPLL pin
Place near VPHY pin

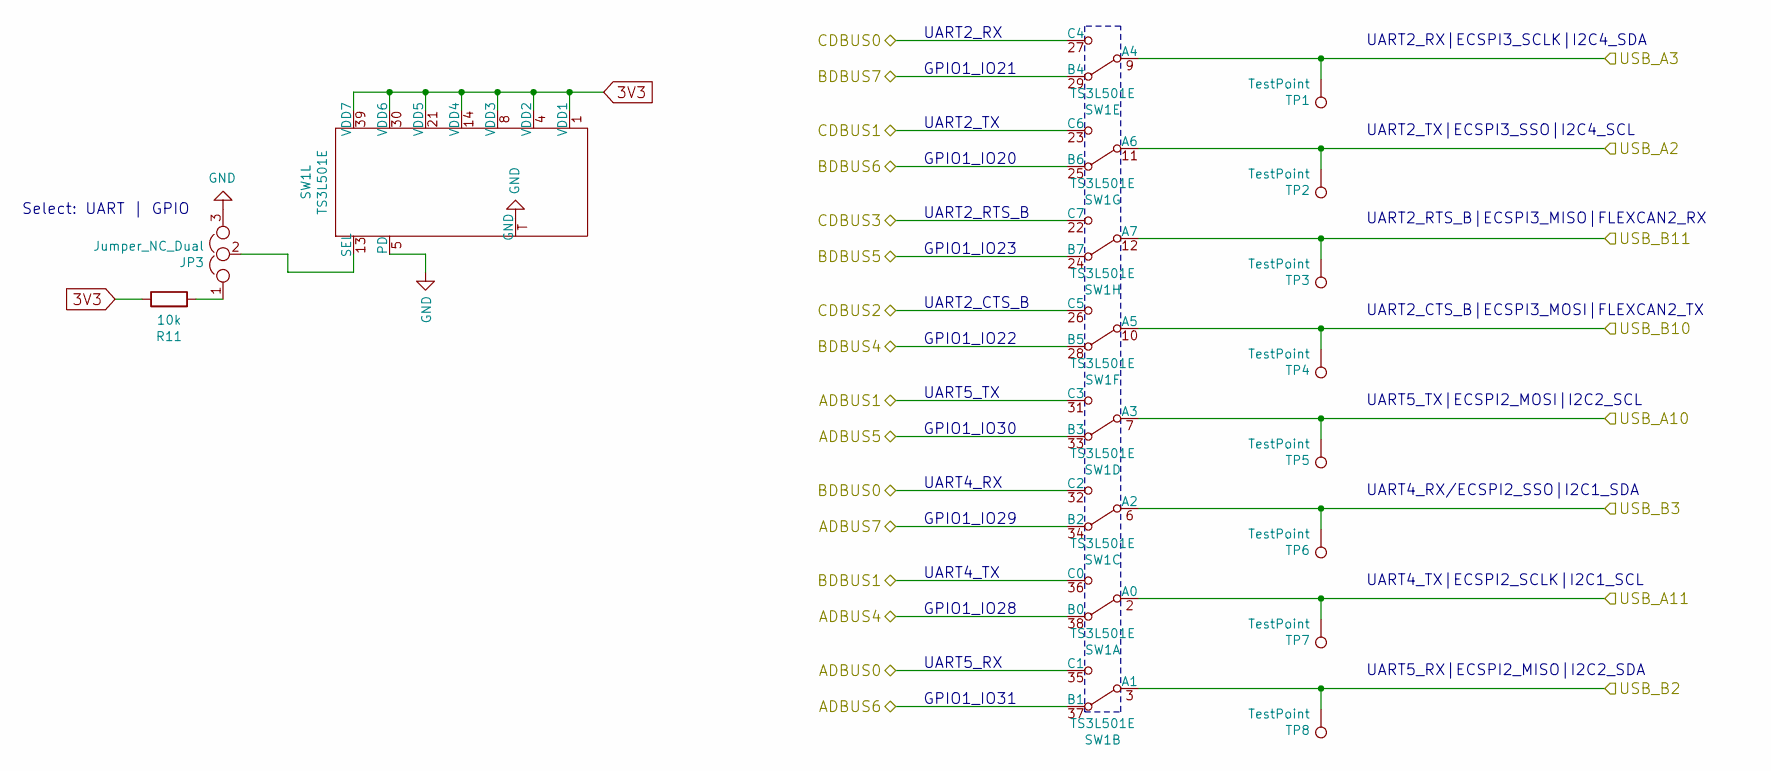
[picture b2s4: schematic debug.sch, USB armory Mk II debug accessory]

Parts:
JP3: Jumper_NC_Dual; SIL-3; Mfg PN 68000-103HLF
R11: 10k; SM0603; Mfg PN CRCW060310K0FKEA
SW1: TS3L501E; R-PWQFN-N42
TP1, TP2, TP3, TP4, TP5, TP6, TP7, TP8: TestPoint; CONN_1

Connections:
3V3: R11.1, SW1.1 (VDD1), SW1.4 (VDD2), SW1.8 (VDD3), SW1.14 (VDD4), SW1.21 (VDD5), SW1.30 (VDD6), SW1.39 (VDD7); also elsewhere on the board
/FTDI/ADBUS0: SW1.35 (C1); also elsewhere on the board
/FTDI/ADBUS1: SW1.31 (C3); also elsewhere on the board
/FTDI/ADBUS4: SW1.38 (B0); also elsewhere on the board
/FTDI/ADBUS5: SW1.33 (B3); also elsewhere on the board
/FTDI/ADBUS6: SW1.37 (B1); also elsewhere on the board
/FTDI/ADBUS7: SW1.34 (B2); also elsewhere on the board
/FTDI/BDBUS0: SW1.32 (C2); also elsewhere on the board
/FTDI/BDBUS1: SW1.36 (C0); also elsewhere on the board
/FTDI/BDBUS4: SW1.28 (B5); also elsewhere on the board
/FTDI/BDBUS5: SW1.24 (B7); also elsewhere on the board
/FTDI/BDBUS6: SW1.25 (B6); also elsewhere on the board
/FTDI/BDBUS7: SW1.29 (B4); also elsewhere on the board
/FTDI/CDBUS0: SW1.27 (C4); also elsewhere on the board
/FTDI/CDBUS1: SW1.23 (C6); also elsewhere on the board
/FTDI/CDBUS2: SW1.26 (C5); also elsewhere on the board
/FTDI/CDBUS3: SW1.22 (C7); also elsewhere on the board
/debug/USB_A2: SW1.11 (A6), TP2.1; also elsewhere on the board
/debug/USB_A3: SW1.9 (A4), TP1.1; also elsewhere on the board
/debug/USB_A10: SW1.7 (A3), TP5.1; also elsewhere on the board
/debug/USB_A11: SW1.2 (A0), TP7.1; also elsewhere on the board
/debug/USB_B2: SW1.3 (A1), TP8.1; also elsewhere on the board
/debug/USB_B3: SW1.6 (A2), TP6.1; also elsewhere on the board
/debug/USB_B10: SW1.10 (A5), TP4.1; also elsewhere on the board
/debug/USB_B11: SW1.12 (A7), TP3.1; also elsewhere on the board
GND: JP3.3, SW1.5 (PD), SW1.T (GND); also elsewhere on the board
unnamed: JP3.1, R11.2
unnamed: JP3.2, SW1.13 (SEL)

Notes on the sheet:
UART2_CTS_B|ECSPI3_MOSI|FLEXCAN2_TX
UART5_TX|ECSPI2_MOSI|I2C2_SCL
UART4_RX/ECSPI2_SSO|I2C1_SDA
UART4_TX|ECSPI2_SCLK|I2C1_SCL
UART5_RX|ECSPI2_MISO|I2C2_SDA
UART2_RTS_B|ECSPI3_MISO|FLEXCAN2_RX
UART2_TX|ECSPI3_SSO|I2C4_SCL
UART2_RX|ECSPI3_SCLK|I2C4_SDA
GPIO1_IO20
GPIO1_IO21
UART2_RX
UART2_TX
UART2_RTS_B
UART2_CTS_B
UART5_TX
UART4_RX
Select: UART | GPIO
UART4_TX
UART5_RX
GPIO1_IO23
GPIO1_IO22
GPIO1_IO30
GPIO1_IO29
GPIO1_IO28
GPIO1_IO31

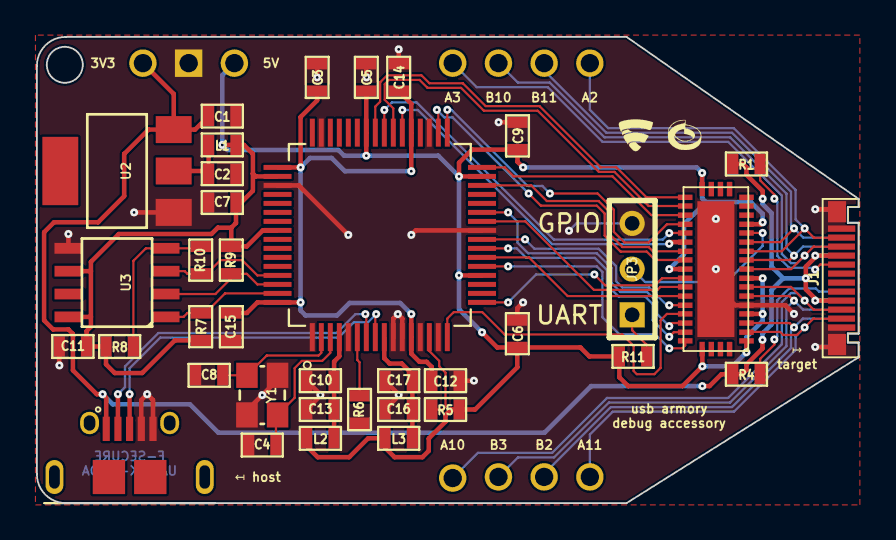
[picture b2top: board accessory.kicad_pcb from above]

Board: 2 copper layers, 45.7 x 25.9 mm, 50 parts (0 on the bottom side), 45 nets.

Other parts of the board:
FSC_LOGO_NO_TEXT_SMALL: G***; FSC_LOGO_NO_TEXT_SMALL
Ref**: Val**; IP_LOGO_NO_TEXT_SMALL

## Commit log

2020-02-04 added files
2020-02-04 pushed files
2020-02-04 made changes
2020-04-04 removed zones
2020-04-04 added zones again
2020-04-04 modified zones
2020-04-06 Backlink to CADLAB.io has been added.
